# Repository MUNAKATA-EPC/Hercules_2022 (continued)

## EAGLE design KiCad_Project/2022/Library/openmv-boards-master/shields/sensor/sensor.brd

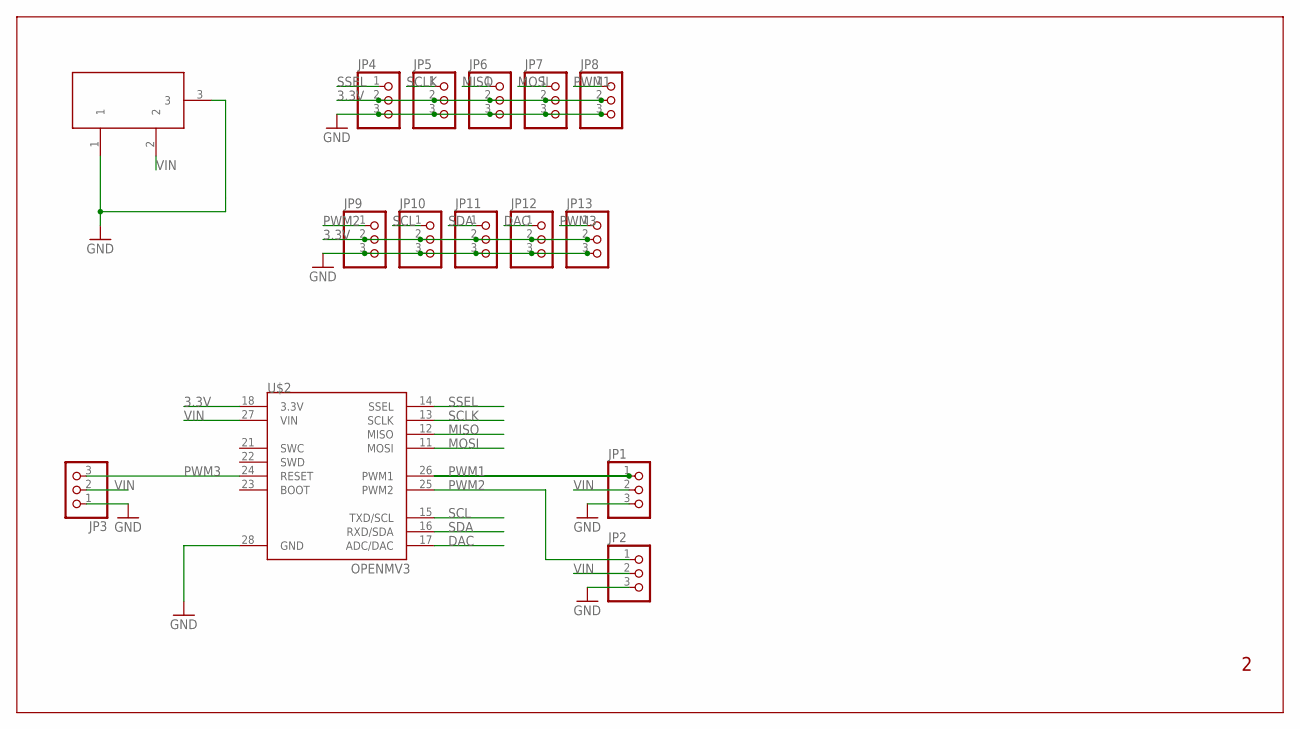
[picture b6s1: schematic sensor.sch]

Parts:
JP1, JP2, JP3, JP4, JP5, JP6, JP7, JP8, JP9, JP10, JP11, JP12, JP13: PINHEAD_PINHD-1X3; PINHEAD_1X03
U$2: OPENMV3
X1: DC21MMX; DC-21MM

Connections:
3.3V: JP4.2, JP5.2, JP6.2, JP7.2, JP8.2, JP9.2, JP10.2, JP11.2, JP12.2, JP13.2, U$2.18 (3.3V)
DAC: JP12.1, U$2.17 (ADC/DAC)
GND: JP1.3, JP2.3, JP3.1, JP4.3, JP5.3, JP6.3, JP7.3, JP8.3, JP9.3, JP10.3, JP11.3, JP12.3, JP13.3, U$2.28 (GND), X1.1, X1.3
MISO: JP6.1, U$2.12 (MISO)
MOSI: JP7.1, U$2.11 (MOSI)
PWM1: JP1.1, JP8.1, U$2.26 (PWM1)
PWM2: JP2.1, JP9.1, U$2.25 (PWM2)
PWM3: JP3.3, JP13.1, U$2.24 (RESET)
SCL: JP10.1, U$2.15 (TXD/SCL)
SCLK: JP5.1, U$2.13 (SCLK)
SDA: JP11.1, U$2.16 (RXD/SDA)
SSEL: JP4.1, U$2.14 (SSEL)
VIN: JP1.2, JP2.2, JP3.2, U$2.27 (VIN), X1.2

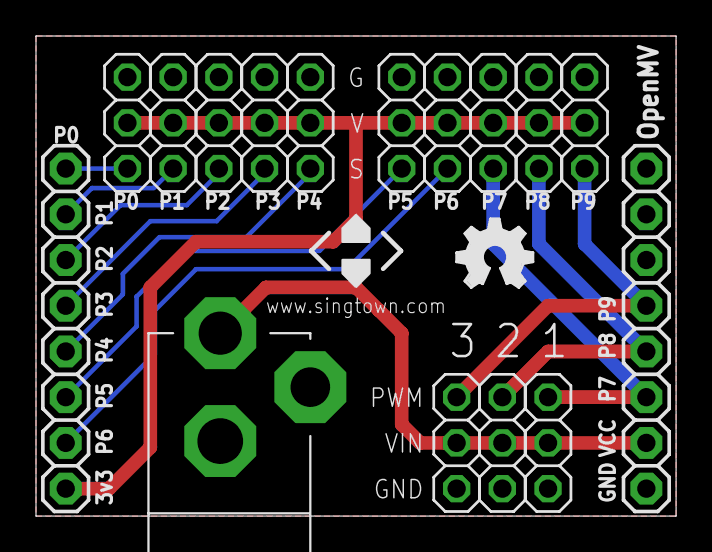
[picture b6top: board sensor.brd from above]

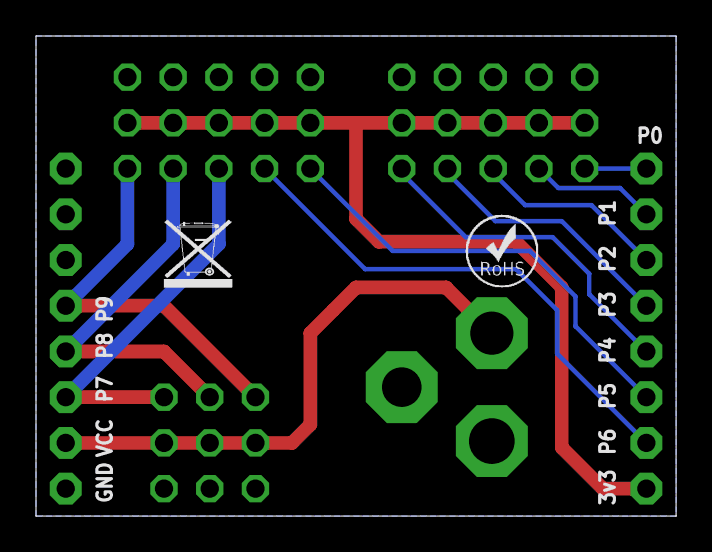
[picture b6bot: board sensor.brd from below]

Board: 2 copper layers, 35.6 x 26.7 mm, 19 parts (2 on the bottom side), 13 nets.

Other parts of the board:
U$1: OSHW_FILLX150_NOTEXT
U$3: ROHS
U$4: WEEE
U$8: SINGTOWN_LOGO; SINGTOWN_5MM

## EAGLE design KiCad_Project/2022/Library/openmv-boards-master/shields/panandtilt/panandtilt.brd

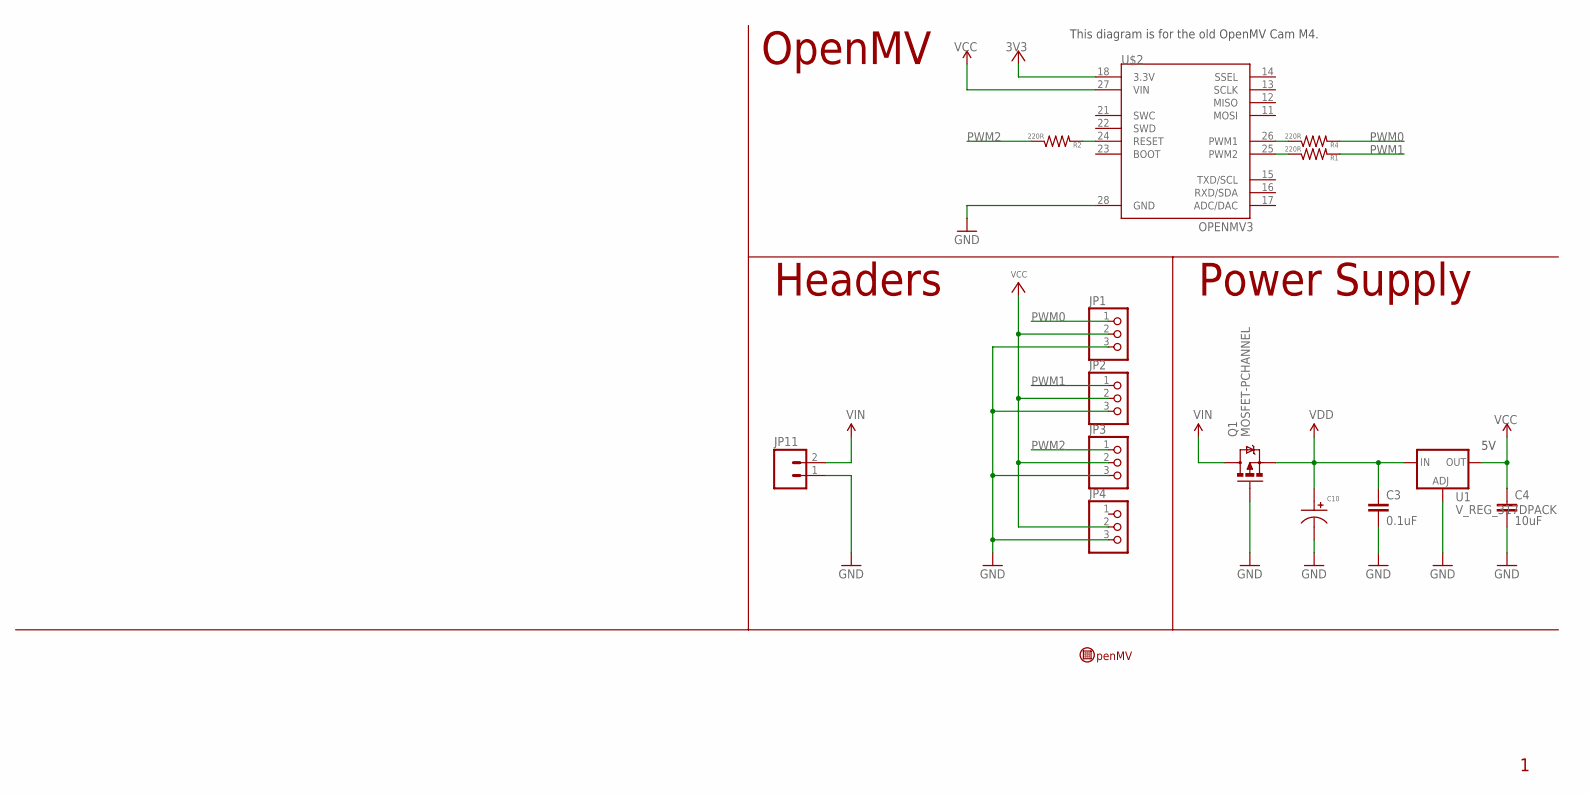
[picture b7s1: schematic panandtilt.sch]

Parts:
C3: 0.1uF; 0603-CAP
C4: 10uF; 0805
C10: CAPACITOR_P_10MM; CP10MM
JP1, JP2, JP3, JP4: PINHD-1X3; 1X03
JP11: M023.5MM; SCREWTERMINAL-3.5MM-2
Q1: MOSFET-PCHANNEL; SOT23-3
R1, R2, R4: 220R; 0603-RES
U1: V_REG_317DPACK; V-REG_DPACK
U$2: OPENMV3
U$9: OPENMV-LOGO

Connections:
3V3: U$2.18 (3.3V)
GND: C3.2, C4.2, C10.P$2, JP1.3, JP2.3, JP3.3, JP4.3, JP11.1, Q1.1 (G), U1.1 (ADJ), U$2.28 (GND)
unnamed: R4.1, U$2.26 (PWM1)
unnamed: R1.1, U$2.25 (PWM2)
unnamed: R2.2, U$2.24 (RESET)
PWM0: JP1.1, R4.2
PWM1: JP2.1, R1.2
PWM2: JP3.1, R2.1
VCC: C4.1, JP1.2, JP2.2, JP3.2, JP4.2, U1.4 (OUT), U$2.27 (VIN)
VDD: C3.1, C10.P$1, Q1.2 (S), U1.3 (IN)
VIN: JP11.2, Q1.3 (D)

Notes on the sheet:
Headers
OpenMV
Power Supply
This diagram is for the old OpenMV Cam M4.

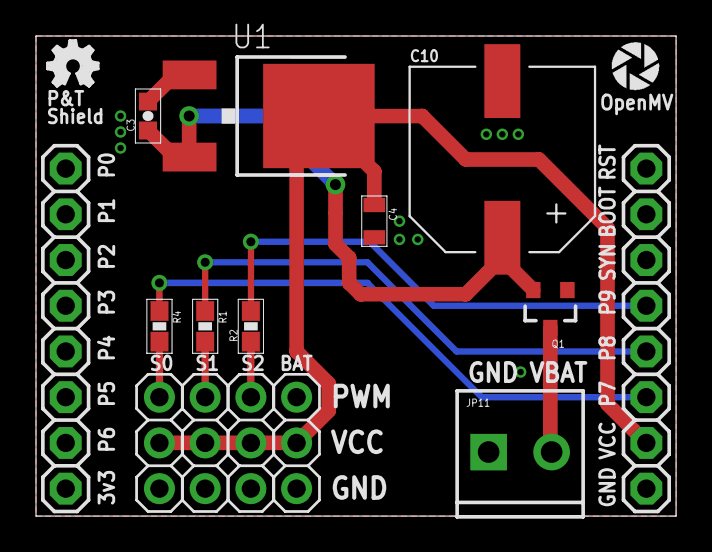
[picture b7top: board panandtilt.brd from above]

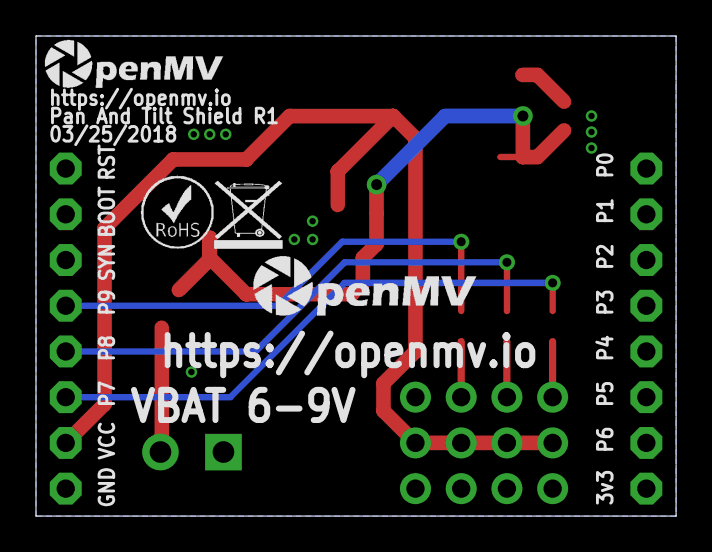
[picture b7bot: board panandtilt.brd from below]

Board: 2 copper layers, 35.6 x 26.7 mm, 20 parts (4 on the bottom side), 10 nets.

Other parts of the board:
U$3: OMV-LOGO
U$5: ROHS
U$6: WEEE
U$10: OMV-LOGO-SMALL
U$11: OSHW_FILLX100_NOTEXT

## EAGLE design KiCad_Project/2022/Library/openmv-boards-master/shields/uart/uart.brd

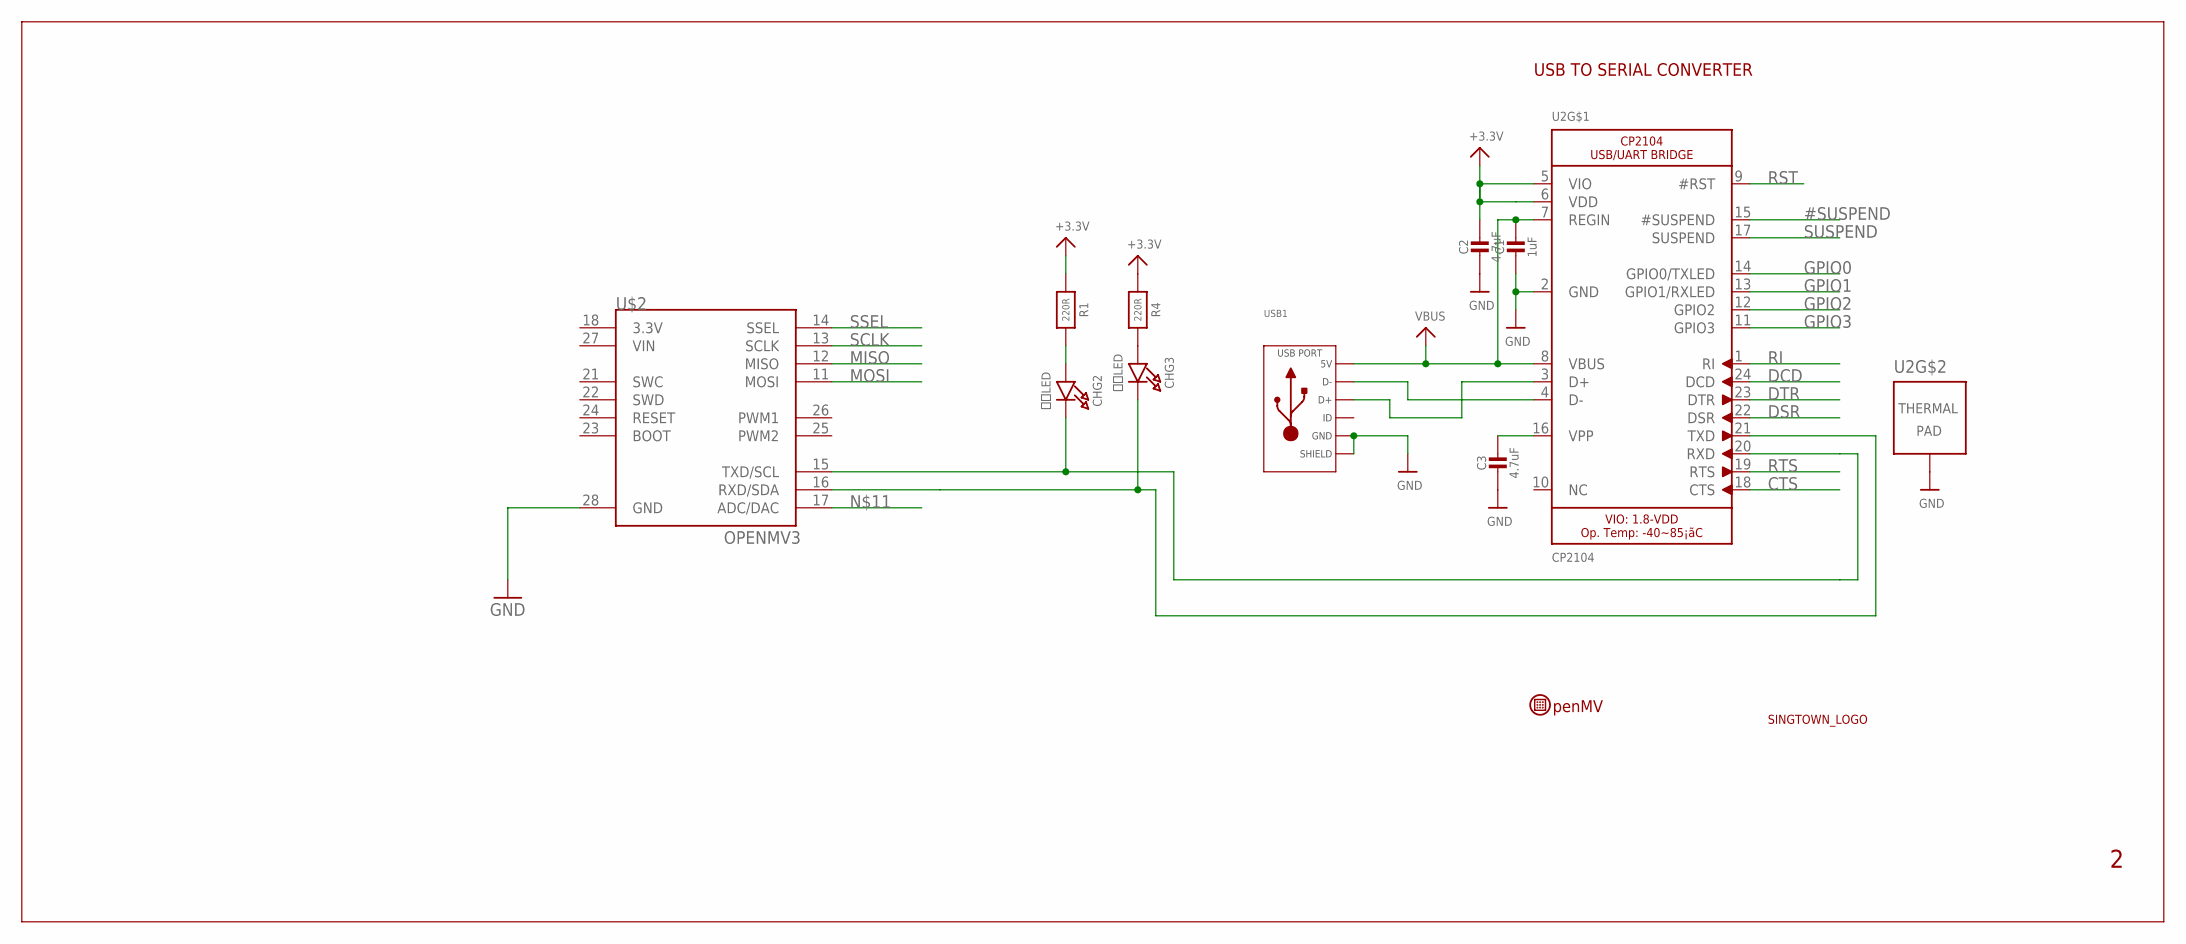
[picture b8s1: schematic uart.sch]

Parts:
C1: 1uF; _0603MP
C2, C3: 4.7uF; _0603MP
CHG2, CHG3: 蓝色LED; CHIPLED_0603_NOOUTLINE
R1, R4: 220R; _0603MP
U2: CP2104; QFN24_4MM_SMSC
U$2: OPENMV3
U$7: OPENMV-LOGO
U$8: SINGTOWN_LOGO; SINGTOWN_5MM
USB1: USB_MICRO_RIGHT; MICROUSB-RIGHT

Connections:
3.3V: C2.1, R1.1, R4.1, U2.5 (VIO), U2.6 (VDD)
#SUSPEND: U2.15 (#SUSPEND)
CTS: U2.18 (CTS)
DCD: U2.24 (DCD)
DSR: U2.22 (DSR)
DTR: U2.23 (DTR)
GND: C1.2, C2.2, C3.2, U2.2 (GND), U2.THERM (TP), U$2.28 (GND), USB1.5 (GND), USB1.S1 (SLD), USB1.S2 (SLD), USB1.S3 (SLD), USB1.S4 (SLD), USB1.S5 (SLD), USB1.S6 (SLD)
GPIO0: U2.14 (GPIO0/TXLED)
GPIO1: U2.13 (GPIO1/RXLED)
GPIO2: U2.12 (GPIO2)
GPIO3: U2.11 (GPIO3)
MISO: U$2.12 (MISO)
MOSI: U$2.11 (MOSI)
unnamed: U2.4 (D-), USB1.2 (D-)
unnamed: U2.3 (D+), USB1.3 (D+)
unnamed: C3.1, U2.16 (VPP)
unnamed: CHG3.C, U2.21 (TXD), U$2.16 (RXD/SDA)
unnamed: CHG2.A, R1.2
unnamed: CHG3.A, R4.2
unnamed: CHG2.C, U2.20 (RXD), U$2.15 (TXD/SCL)
RI: U2.1 (RI)
RST: U2.9 (#RST)
RTS: U2.19 (RTS)
SCLK: U$2.13 (SCLK)
SSEL: U$2.14 (SSEL)
SUSPEND: U2.17 (SUSPEND)
VBUS: C1.1, U2.7 (REGIN), U2.8 (VBUS), USB1.1 (5V)

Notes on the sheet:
USB TO SERIAL CONVERTER

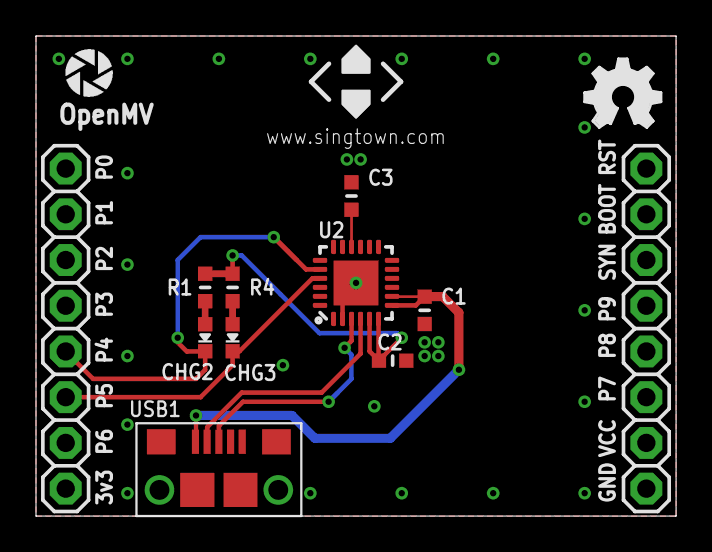
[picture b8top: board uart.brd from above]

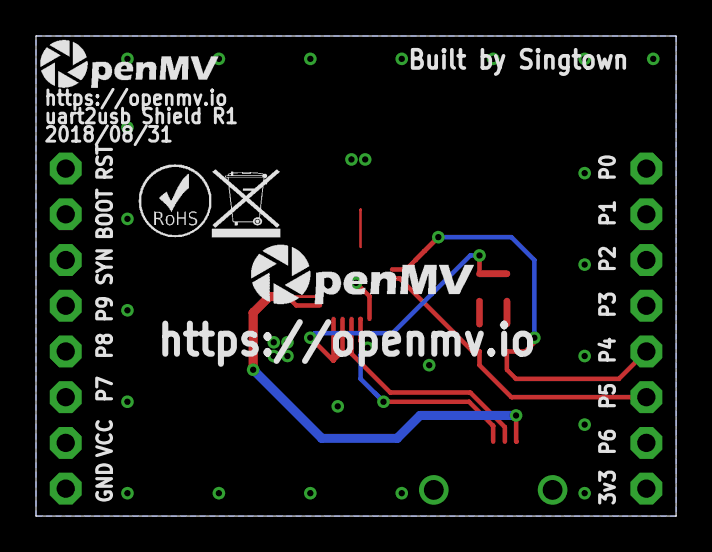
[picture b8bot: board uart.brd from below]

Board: 2 copper layers, 35.6 x 26.7 mm, 17 parts (4 on the bottom side), 10 nets.

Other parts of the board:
U$1: OSHW_FILLX150_NOTEXT
U$13: OMV-LOGO-SMALL
U$14: ROHS
U$15: WEEE
U$16: OMV-LOGO

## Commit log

2021-12-26 Create LICENSE
2021-12-26 ふじたきよゆきが編集しました
2021-12-26 メッセージ削除
2021-12-26 スペースが増えたよ！(見づらくて草)
2021-12-26 編集してみました
2021-12-27 説明を増やしました
2021-12-27 作りかけです
2021-12-27 あとは各種モーターの値を設定してあげてください
2021-12-27 表示内容を変更しました
2021-12-27 IMUの値反転とCAM情報取得処理を追加
2021-12-27 CAMとPID制御用の変数を追加
2021-12-27 ラインやカメラ角度などのおおまかな骨組みを作成
2021-12-27 test.cppなんてなかった。いいね？
2021-12-27 テストコメントの削除
2021-12-27 スペースが減ったよ
2021-12-27 PID設定してね
2021-12-27 色々調整入れました
2021-12-27 なんちゃってクラス導入
2021-12-27 ちょっとずつ変わったで
2021-12-28 PID制御実装
2021-12-28 モーター限界値設定をMotor各関数内で行うようにしました
2021-12-28 LCD切り替えスイッチを押すと、プログラムの実行状態が必ず解除されるようになりました
2021-12-28 MD準備開始位置の変更と、OpenMVとの通信を行えるようにしました
2021-12-28 USBシリアル通信の速度を115200bpsに統一しました
2021-12-30 定位置用の情報は送らないようにしました。そして、送信が完了するまで待機するようになります。
2021-12-30 クラスにまとめました
2022-01-02 KiCadプロジェクトファイルの作成
2022-01-05 自分好みに変えました
2022-01-05 コメント位置が変わりました
2022-01-05 私好みになりました
2022-01-05 PIDパラメータ値をここで変えれるようにしました
2022-01-05 誤動作防止処理を追加しました
2022-01-05 クラスの表記がまとまったり、ゲイン値が消えたり
2022-01-05 ライブラリとヘッダファイルで表記を変えました
2022-01-06 コードの最適化
2022-01-06 コードの最適化(変数被りの除去)
2022-01-06 変数被り防止
2022-01-06 変数被り防止とメモリ使用量削減
2022-01-06 ピン番号の修正
2022-01-06 Source Treeテストコメントの追加
2022-01-06 テストコメント削除
2022-01-07 トグルスイッチの役割をモード固定的なものへと変更しました
2022-01-07 モーターモードに姿勢制御を実装
2022-01-07 操作量の上限値、下限値の見直し
2022-01-07 操作量上限値とモーター速度がパラメータ設定から変更可能になりました
2022-01-07 モーター速度をパラメータに置き換えました
2022-01-07 モーター速度限界値をパラメータから調整できるようになりました
2022-01-08 PID制御を一時的に外してます
2022-01-08 タイプミス修正
2022-01-08 パラメータを変数化
2022-01-08 PID制御の読み込みを一時的に外しました
2022-01-13 方向判定の変数化
2022-01-13 LCD表示バグの修正
2022-01-13 方向判定の仕様変更
2022-01-15 出力バランス調整
2022-01-15 関数呼び出し時にどの値が何なのかわかるようにコメントを追加
2022-01-16 IMU閾値を読み込み専用に変更
2022-01-18 アナログ出力分解能を変更
2022-01-19 開発間に合わないんで
2022-01-19 ミス修正とか色々
2022-01-19 走り抜けるぜッ！最後まで
2022-01-19 gotoの削除
2022-01-19 処理の仕様変更
2022-01-19 変数の追加と削除
2022-01-19 loop関数内は全て条件分岐での動作に変更
2022-01-20 回路関係のファイルをGitにまとめました
    発注ファイルとDFXでごちゃごちゃしてるのはすいません
2022-01-20 統合電源基板
2022-01-21 処理の若干の変更
2022-01-21 色々微調整
2022-01-21 nakamoto的メインプログラム
2022-01-21 ライブラリの追加
2022-01-21 EMI対策とDCDCの周辺設計
    過電流保護機能・加熱保護機能付き
    可変抵抗で出力の変更可能
2022-01-21 回路図の完成
2022-01-22 仕様変更
2022-01-22 ラインセンサをデジタルで読むように変更
2022-01-22 IMUの範囲調整
2022-01-22 メインプログラム(仮)
2022-01-22 RCAPで開発した遺産たち
2022-01-22 MPU遺産削除
2022-01-22 MPU6050用のXiaoプログラム
2022-01-22 定位置が動作しないおそれのある不具合を修正
2022-01-22 OpenMVプログラムの移植
2022-01-22 定位置の変更
2022-01-23 九州ブロック 本番調整
2022-01-23 カメラ通信の安定化
2022-01-23 コネクタの逆差し対策
    ショットキーバリスタダイオードでDCDCよりも前に素早く短絡させます
2022-01-24 プチ変更
2022-01-27 九州ブロックでのやつ
2022-01-29 PID制御のリベンジとクラスの追加
2022-01-29 ライブラリを初期化
2022-01-29 このリポジトリのライセンスについて
2022-01-30 Update LICENSE
2022-02-01 電源統合基板の進捗
2022-02-05 Kicadプロジェクトの整理
    ファイルについて
    各基板のプロジェクト・ライブラリ・PDF・DXF・自動配線用・発注ファイル
    に分けました。
    またライブラリのインポートに際してプロフェクトからの相対パスに変更したため環境を変更しても編集することができます。
2022-02-05 keep
2022-02-05 環境設定
2022-02-07 電源系の設計の完了
    ATtinyを使って電圧を測定してシリアルでメインマイコンに送信します
    レベル変換についてはまだ考えてない
2022-02-09 部品の配置
2022-02-10 ビアを追加してノイズ対策
2022-02-12 統合電源基板の設計の完了
2022-02-13 設計図資料の更新と発注用ファイルの作成
2022-02-15 ごちゃごちゃ感が若干改善された
2022-02-15 回り込みの関数化
2022-02-15 積分値の初期化範囲の設定
2022-02-15 発注ファイルの設定の変更
2022-02-17 視認性が向上？
2022-02-17 データの受信仕様変更
2022-02-19 メンテナンス性の向上
2022-02-19 回り込みの仕様変更とか
2022-02-24 マウスセンサの設計の完了
    ADNS－9800使用
    SeeeduinoXIAOを用いてUARTでメインマイコンと通信
2022-03-01 メインボードの開発
2022-03-01 READMEの編集
2022-03-10 Startupをmain内に移動
2022-03-14 Teensy4.0_Breakout_Board
2022-03-18 メインボードの進捗
2022-03-19 MPU6050ジャイロ仕様変更
2022-03-19 VSCode拡張機能関係の追加
2022-03-19 PID制御をごにょごにょしたやつ
2022-03-19 PID周りをごにょごにょ
2022-03-19 変更点のコミット
2022-03-21 ライブラリの参照問題？
2022-03-22 マウス基板の改良
2022-03-22 バックアップ
2022-03-22 ライブラリの編集
2022-03-22 ライブラリの参照問題
2022-03-22 徹夜の進捗、朝マック食べに行きます
2022-03-23 フットプリントライブラリの編集
2022-03-25 フットプリントの割り当てまで終わった
2022-03-26 DXFの出力
2022-03-27 PID制御のある程度の仕様固め
2022-03-27 switch caseに置き換え
2022-03-27 回り込み調整段階
2022-03-27 最終的な基板の完成
2022-03-28 レジストを抜いて文字とURLを記入
2022-03-28 基板発注が完了しました
    ちなみに合計金額8000円でした
2022-03-29 PDFの作成
2022-04-02 クソ雑魚PD制御
2022-04-02 フィールドの緑色を使うようになりました
2022-04-02 フィールドの緑色をカラートラッキングできるようになりました
2022-04-02 変数名の誤り訂正
2022-04-02 親愛なるロボカッパーたちへ ゴールのトラッキング機能も仮実装されました わずかなステップで黄色と青色もカラートラッキングの対象に含めることが出来ます
2022-04-08 カメラ仮調整
2022-04-08 回り込みとショートブレーキの仕様変更
2022-04-08 PD制御調整
2022-04-08 グローバル変数と定数の置き場所を変更
2022-04-08 LCDがエラー情報を吐くように変更
2022-04-16 PIDパラメータ確定
2022-04-16 回り込み大雑把だけど確定
2022-04-16 色の閾値仮決め
2022-04-16 けいはんな機ソフトウェアの骨組み的なところ組んだ
2022-04-17 ピン番号とLCD表示位置の仮決め
2022-04-21 新造機向けにファーム書き換え
2022-04-21 USBシリアルを追加
2022-04-21 新ライブラリのインストール
2022-04-22 新造機向けファーム改造(カメラの値の出方が左右逆になっている現象に対処)
2022-04-22 なんかよくわからん(VSCodeが勝手に変更しやがった)
2022-04-22 使わないライブラリの消去
2022-04-22 なんやねんコイツ
2022-04-22 プログラムの最適化と新規オフセット値の適用
2022-04-23 大会中変更1(マキシマムモード()実装と回り込みの3分割化)
2022-04-28 READMEにコードとライセンスに関する内容を追記
2022-04-29 ジャパンで実装したところ全て
2022-05-08 Teensy 4.0の動作周波数OC環境の追加
2022-05-08 ジャパンオープンけいはんな2022ベースで外部からの無線通信による操作に対応
2022-05-08 眠ってたM5StickCちゃんを供養しようの会
2022-05-08 無線機、格ゲーコントローラーver
2022-05-08 無線機、ジョイコントローラー的なやつで操縦するver
2022-05-08 M5StickCの電圧を確認するためだけのやつ
2022-05-08 電圧状況に応じて文字色が変わるよ
2022-05-30 Update README.md
    スペルミス訂正
2022-07-20 文字の色変わる仕様、やっぱりなしの方向で
2022-07-20 表示色を白で統一
2022-07-20 色々細かくバグ取り(バグ取り)
2022-07-20 GyroController用受信側Picoのプログラム
2022-07-20 PS3コントローラーとPicoを接続して自律機を無線機化するプロジェクトから生まれた何か
2023-03-31 VSCodeからのテストコミット
